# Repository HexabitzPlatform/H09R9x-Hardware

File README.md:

# H09R9x-Hardware
Hexabitz Thermopile Sensor Module Hardware Design

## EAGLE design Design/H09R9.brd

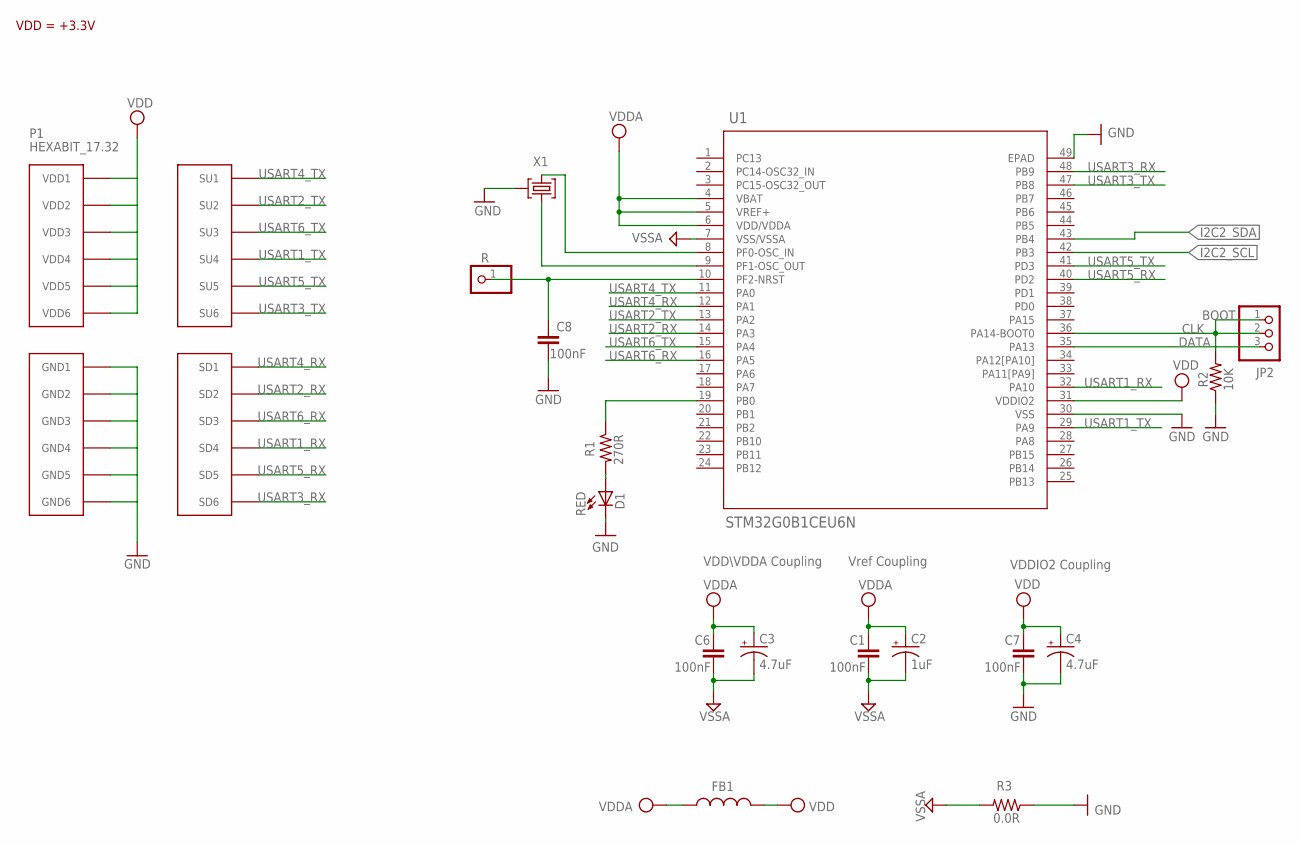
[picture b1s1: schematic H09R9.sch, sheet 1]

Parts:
C1, C6, C7, C8: 100nF; C-0603
C2: 1uF; C-0805-POL
C3, C4: 4.7uF; C-0805-POL
D1: RED; VLMS1300-GS08; MPN VLMS1300-GS08
FB1: FB-TDK_MMZ1608Y300B; MPN MMZ1608Y300B
JP2: PINHD-1X3; 1X03
P1: HEXABIT_17.32
R: R; 1X01
R1: 270R; R-0603
R2: 10K; R-0603
R3: 0.0R; R-0603; MPN RC0603JR-070RL
U1: STM32G0B1CEU6N; HEXABITZ_ICS_QFN_B1CEU6_STM-L
X1: XTALL_CSTCE8M00G52

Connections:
CLK: JP2.1, JP2.2, R2.2, U1.36 (PA14-BOOT0)
DATA: JP2.3, U1.35 (PA13)
GND: C4.2 (-), C7.2, C8.2, D1.C, P1.PAD_PD7 (GND1), P1.PAD_PD8 (GND2), P1.PAD_PD9 (GND3), P1.PAD_PD10 (GND4), P1.PAD_PD11 (GND5), P1.PAD_PD12 (GND6), R2.1, R3.1, U1.30 (VSS), U1.49 (EPAD), X1.P$2 (2); also elsewhere on the board
I2C2_SCL: U1.42 (PB3); also elsewhere on the board
I2C2_SDA: U1.43 (PB4); also elsewhere on the board
unnamed: R1.1, U1.19 (PB0)
unnamed: D1.A, R1.2
unnamed: C8.1, R.1, U1.10 (PF2-NRST)
unnamed: U1.9 (PF1-OSC_OUT), X1.P$1 (1)
unnamed: U1.8 (PF0-OSC_IN), X1.P$3 (3)
USART1_RX: P1.PAD_PD4 (SD4), U1.32 (PA10)
USART1_TX: P1.PAD_PU4 (SU4), U1.29 (PA9)
USART2_RX: P1.PAD_PD2 (SD2), U1.14 (PA3)
USART2_TX: P1.PAD_PU2 (SU2), U1.13 (PA2)
USART3_RX: P1.PAD_PD6 (SD6), U1.48 (PB9)
USART3_TX: P1.PAD_PU6 (SU6), U1.47 (PB8)
USART4_RX: P1.PAD_PD1 (SD1), U1.12 (PA1)
USART4_TX: P1.PAD_PU1 (SU1), U1.11 (PA0)
USART5_RX: P1.PAD_PD5 (SD5), U1.40 (PD2)
USART5_TX: P1.PAD_PU5 (SU5), U1.41 (PD3)
USART6_RX: P1.PAD_PD3 (SD3), U1.16 (PA5)
USART6_TX: P1.PAD_PU3 (SU3), U1.15 (PA4)
VDD: C4.1 (+), C7.1, FB1.2, P1.PAD_PU7 (VDD1), P1.PAD_PU8 (VDD2), P1.PAD_PU9 (VDD3), P1.PAD_PU10 (VDD4), P1.PAD_PU11 (VDD5), P1.PAD_PU12 (VDD6), U1.31 (VDDIO2); also elsewhere on the board
VDDA: C1.1, C2.1 (+), C3.1 (+), C6.1, FB1.1, U1.4 (VBAT), U1.5 (VREF+), U1.6 (VDD/VDDA)
VSSA: C1.2, C2.2 (-), C3.2 (-), C6.2, R3.2, U1.7 (VSS/VSSA)

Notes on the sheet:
VDD = +3.3V
Vref Coupling
VDDIO2 Coupling
VDD\VDDA Coupling
BOOT

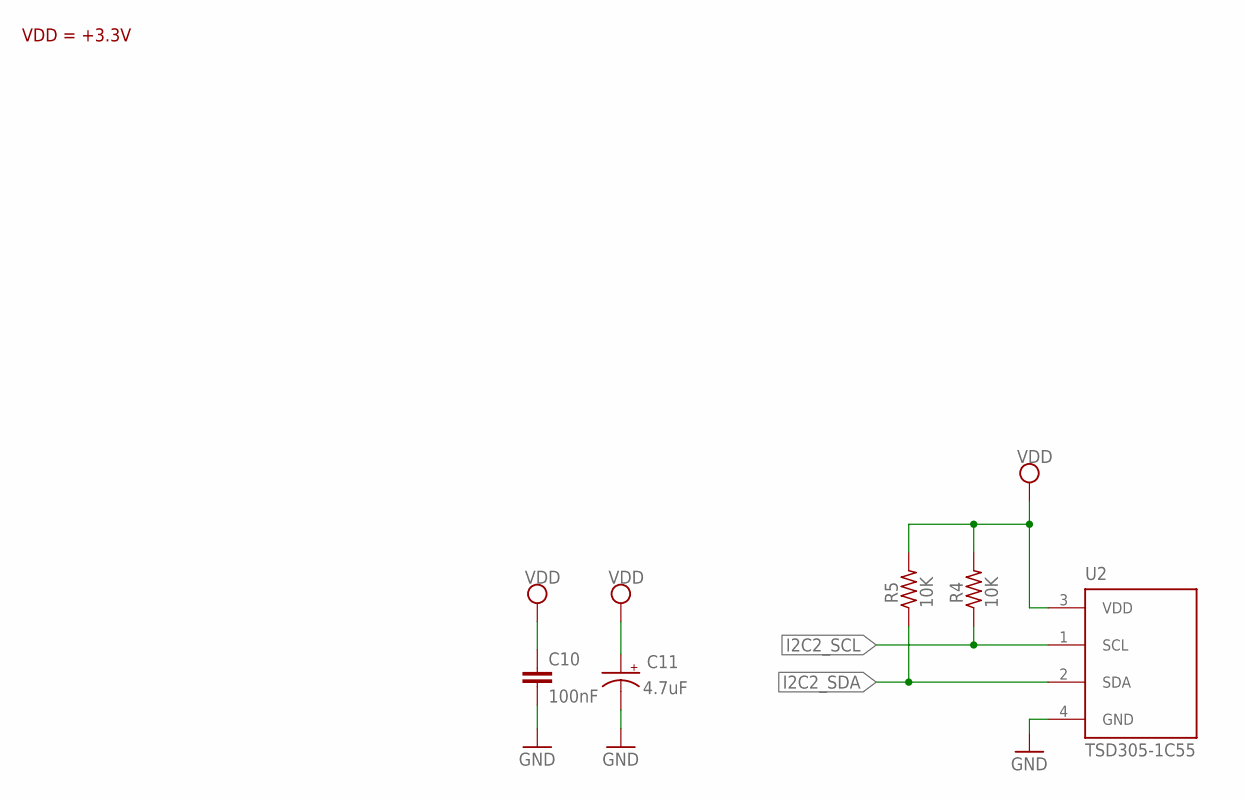
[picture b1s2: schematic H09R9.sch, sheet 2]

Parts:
C10: 100nF; C-0603; TOLERANCE 10%; VOLTAGE_RATING 16.0 V; MPN 0603YC104K4T2A
C11: 4.7uF; C-0805-POL; TOLERANCE 20%; VOLTAGE_RATING 10.0 V; MPN 10TPU4R7MSI
R4, R5: 10K; R-0603
U2: TSD305-1C55; TEMPERATURESENSOR-TO5

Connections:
GND: C10.2, C11.2 (-), U2.4 (GND); also elsewhere on the board
I2C2_SCL: R4.1, U2.1 (SCL); also elsewhere on the board
I2C2_SDA: R5.1, U2.2 (SDA); also elsewhere on the board
VDD: C10.1, C11.1 (+), R4.2, R5.2, U2.3 (VDD); also elsewhere on the board

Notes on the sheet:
VDD = +3.3V

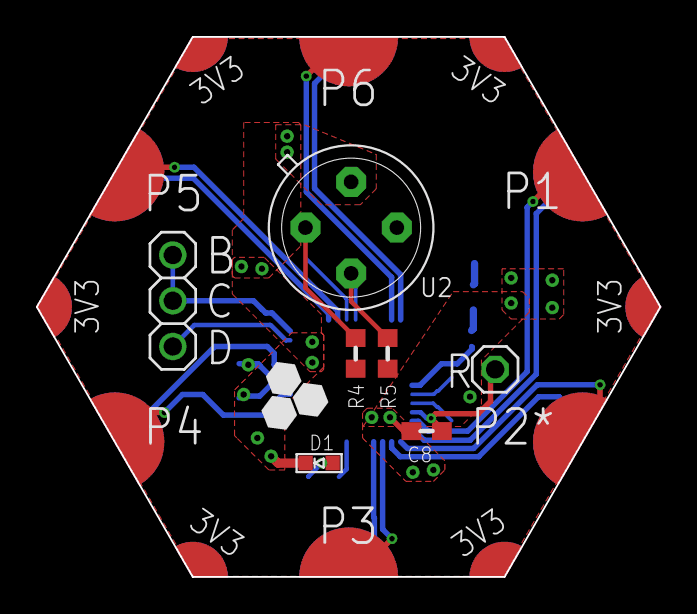
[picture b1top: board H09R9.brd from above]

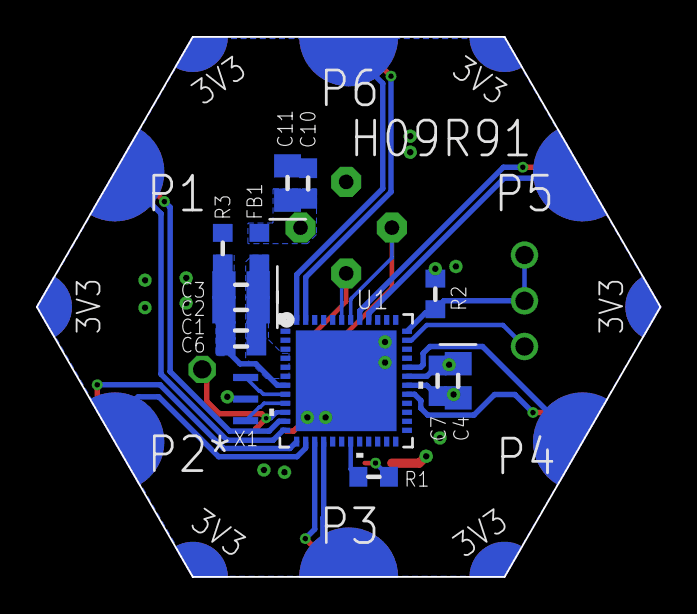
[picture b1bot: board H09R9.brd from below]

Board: 2 copper layers, 34.6 x 30.0 mm, 22 parts (14 on the bottom side), 25 nets.

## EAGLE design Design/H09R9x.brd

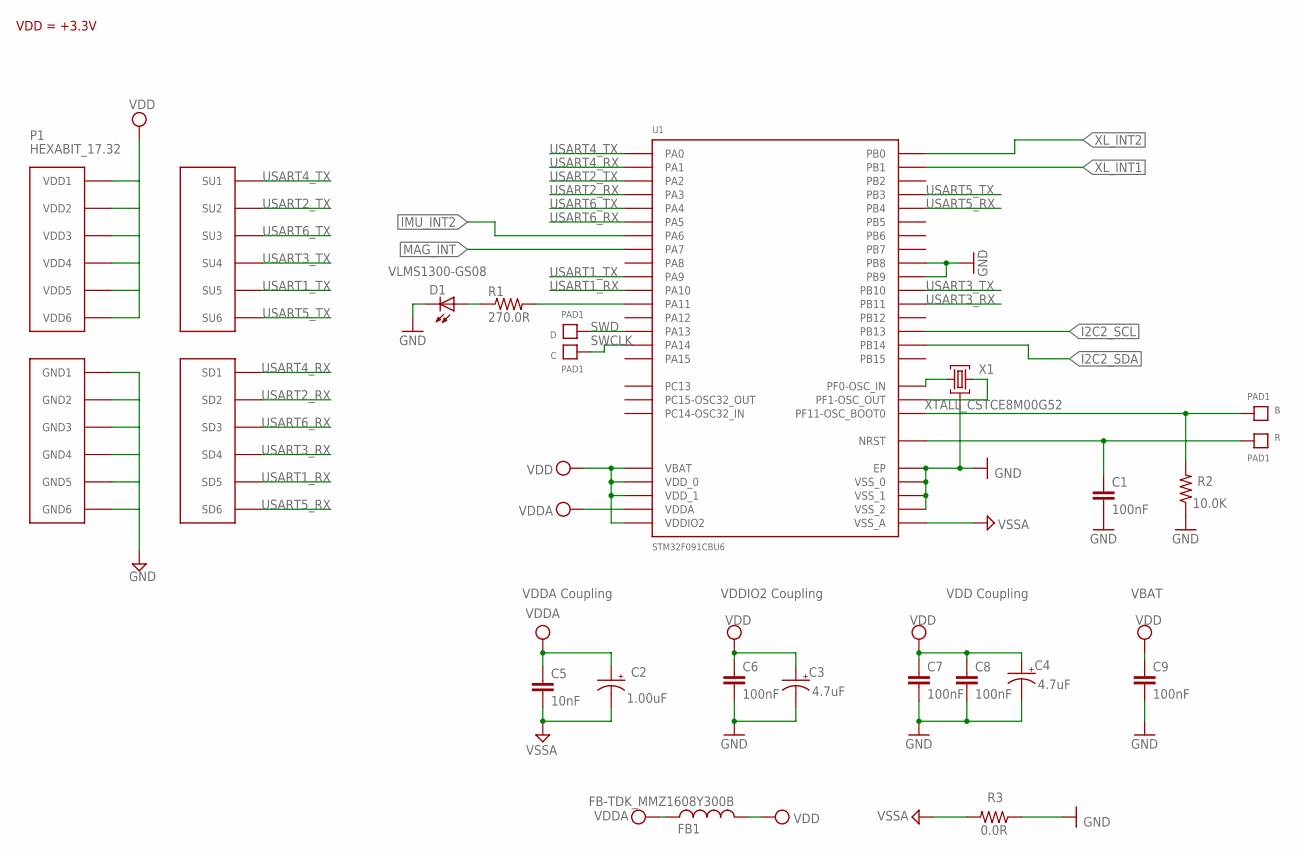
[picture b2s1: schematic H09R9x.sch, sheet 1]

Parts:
B: PAD1
C: PAD1
C1, C6, C7, C8: 100nF; C-0603; TOLERANCE 10%; VOLTAGE_RATING 16.0 V; MPN 0603YC104K4T2A
C2: 1.00uF; C-0805-POL; TOLERANCE 10%; VOLTAGE_RATING 16.0 V; MPN TAJR105M016RNJ
C3: 4.7uF; C-0805-POL; TOLERANCE 20%; VOLTAGE_RATING 10.0 V; MPN 10TPU4R7MSI
C4: 4.7uF; C-0805-POL; TOLERANCE 10%; VOLTAGE_RATING 10 V; MPN 10TPU4R7MSI
C5: 10nF; C-0603; TOLERANCE 10%; VOLTAGE_RATING 16.0 V; MPN 0603YC103KAT4A
C9: 100nF; C-0603; TOLERANCE 16.0 V; VOLTAGE_RATING 10%; MPN 0603YC104K4T2A
D: PAD1
D1: VLMS1300-GS08; MPN VLMS1300-GS08
FB1: FB-TDK_MMZ1608Y300B; MPN MMZ1608Y300B
P1: HEXABIT_17.32
R: PAD1
R1: 270.0R; R-0603; TOLERANCE 5%; MPN ERJ-3GEYJ271V
R2: 10.0K; R-0603; TOLERANCE 5%; MPN CRCW060310K0JNEB
R3: 0.0R; R-0603; MPN CRCW06030000Z0EAHP
U1: STM32F091CBU6
X1: XTALL_CSTCE8M00G52

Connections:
B1: B.P$1, B.P$2, R2.2, U1.P$44 (PF11-OSC_BOOT0)
GND: C1.2, C3.2 (-), C4.2 (-), C6.2, C7.2, C8.2, C9.2, D1.C, P1.PAD_PD7 (GND1), P1.PAD_PD8 (GND2), P1.PAD_PD9 (GND3), P1.PAD_PD10 (GND4), P1.PAD_PD11 (GND5), P1.PAD_PD12 (GND6), R2.1, R3.1, U1.EP, U1.P$23 (VSS_0), U1.P$35 (VSS_1), U1.P$45 (PB8), U1.P$46 (PB9), U1.P$47 (VSS_2), X1.P$2 (2); also elsewhere on the board
I2C2_SCL: U1.P$26 (PB13); also elsewhere on the board
I2C2_SDA: U1.P$27 (PB14); also elsewhere on the board
IMU_INT2: U1.P$16 (PA6)
MAG_INT: U1.P$17 (PA7)
unnamed: R1.2, U1.P$32 (PA11)
unnamed: D1.A, R1.1
unnamed: U1.P$5 (PF0-OSC_IN), X1.P$1 (1)
unnamed: U1.P$6 (PF1-OSC_OUT), X1.P$3 (3)
R1: C1.1, R.P$1, R.P$2, U1.P$7 (NRST)
SWCLK: C.P$1, C.P$2, U1.P$37 (PA14)
SWD: D.P$1, D.P$2, U1.P$34 (PA13)
USART1_RX: P1.PAD_PD5 (SD5), U1.P$31 (PA10)
USART1_TX: P1.PAD_PU5 (SU5), U1.P$30 (PA9)
USART2_RX: P1.PAD_PD2 (SD2), U1.P$13 (PA3)
USART2_TX: P1.PAD_PU2 (SU2), U1.P$12 (PA2)
USART3_RX: P1.PAD_PD4 (SD4), U1.P$22 (PB11)
USART3_TX: P1.PAD_PU4 (SU4), U1.P$21 (PB10)
USART4_RX: P1.PAD_PD1 (SD1), U1.P$11 (PA1)
USART4_TX: P1.PAD_PU1 (SU1), U1.P$10 (PA0)
USART5_RX: P1.PAD_PD6 (SD6), U1.P$40 (PB4)
USART5_TX: P1.PAD_PU6 (SU6), U1.P$39 (PB3)
USART6_RX: P1.PAD_PD3 (SD3), U1.P$15 (PA5)
USART6_TX: P1.PAD_PU3 (SU3), U1.P$14 (PA4)
VDD: C3.1 (+), C4.1 (+), C6.1, C7.1, C8.1, C9.1, FB1.2, P1.PAD_PU7 (VDD1), P1.PAD_PU8 (VDD2), P1.PAD_PU9 (VDD3), P1.PAD_PU10 (VDD4), P1.PAD_PU11 (VDD5), P1.PAD_PU12 (VDD6), U1.P$1 (VBAT), U1.P$24 (VDD_0), U1.P$36 (VDDIO2), U1.P$48 (VDD_1); also elsewhere on the board
VDDA: C2.1 (+), C5.1, FB1.1, U1.P$9 (VDDA)
VSSA: C2.2 (-), C5.2, R3.2, U1.P$8 (VSS_A)
XL_INT1: U1.P$19 (PB1)
XL_INT2: U1.P$18 (PB0)

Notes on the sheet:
VDDA Coupling
VDDIO2 Coupling
VDD Coupling
VBAT
VDD = +3.3V

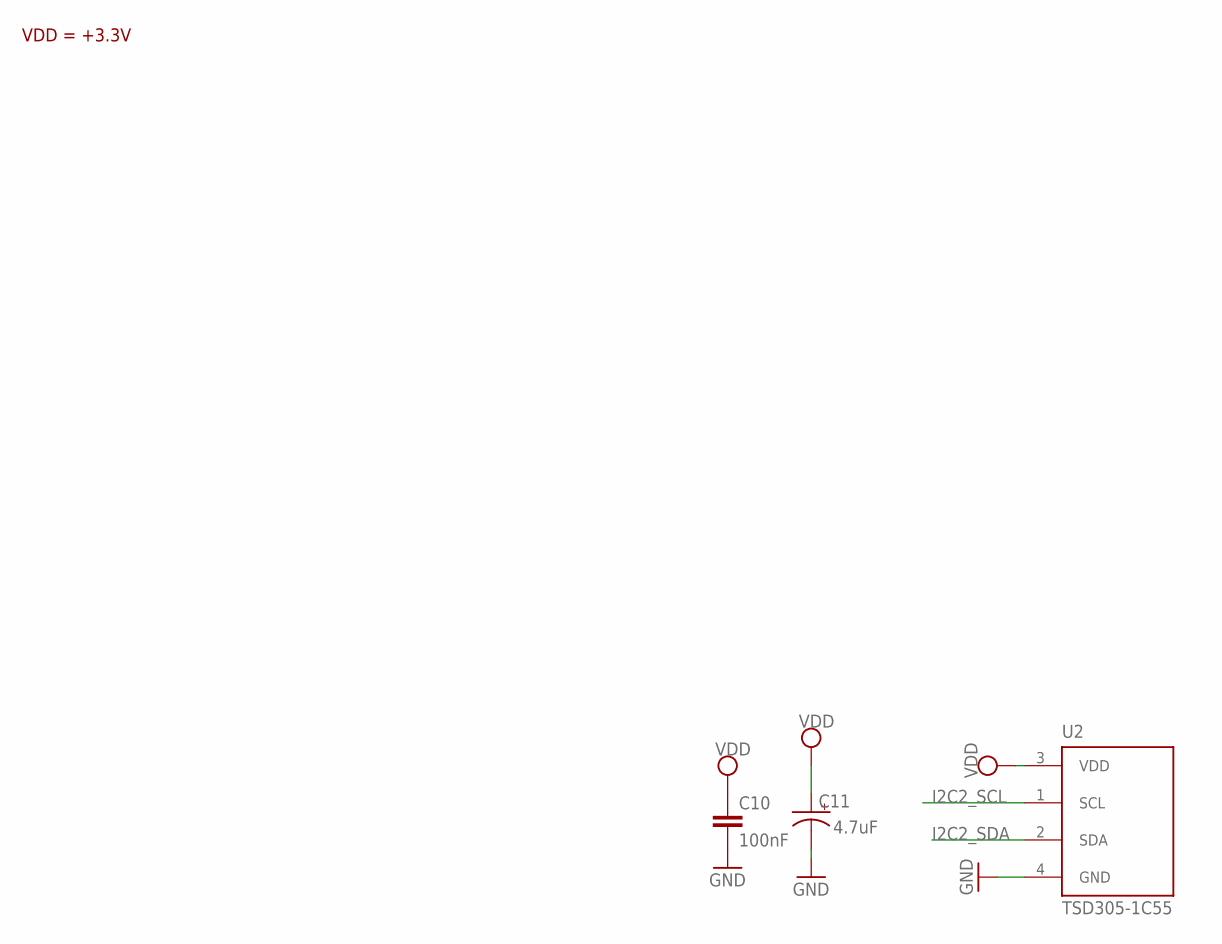
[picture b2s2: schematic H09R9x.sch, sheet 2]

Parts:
C10: 100nF; C-0603; TOLERANCE 10%; VOLTAGE_RATING 16.0 V; MPN 0603YC104K4T2A
C11: 4.7uF; C-0805-POL; TOLERANCE 20%; VOLTAGE_RATING 10.0 V; MPN 10TPU4R7MSI
U2: TSD305-1C55; TEMPERATURESENSOR-TO5

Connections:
GND: C10.2, C11.2 (-), U2.4 (GND); also elsewhere on the board
I2C2_SCL: U2.1 (SCL); also elsewhere on the board
I2C2_SDA: U2.2 (SDA); also elsewhere on the board
VDD: C10.1, C11.1 (+), U2.3 (VDD); also elsewhere on the board

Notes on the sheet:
VDD = +3.3V

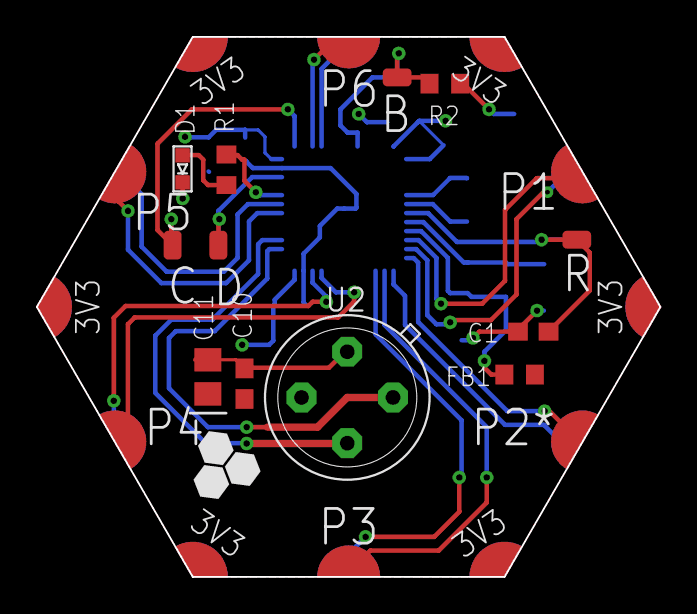
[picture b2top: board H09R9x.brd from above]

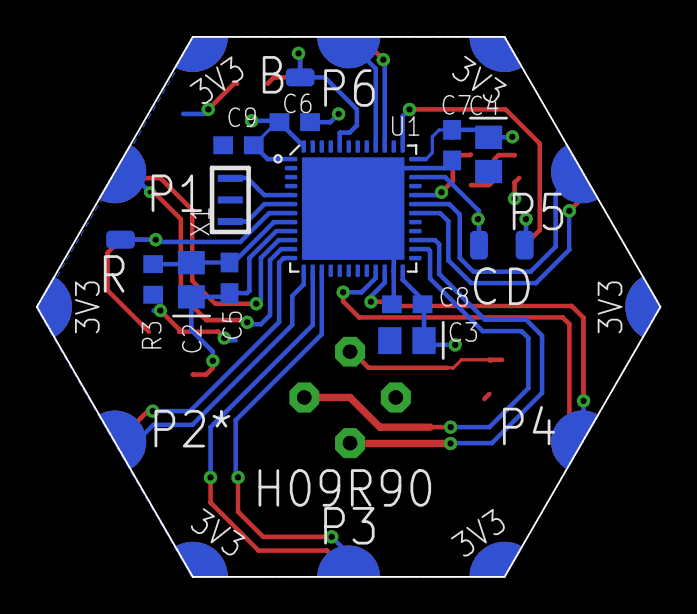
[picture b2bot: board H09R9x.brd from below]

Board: 2 copper layers, 34.6 x 30.0 mm, 24 parts (11 on the bottom side), 26 nets.

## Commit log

2021-03-21 first schematic
2021-03-21 first edit
2021-03-21 not routing yet
2021-03-28 first version sch brd .
2021-03-30 empty
2021-03-31 brd edit
2021-04-16 edit brd
2021-04-20 data upload
2021-04-20 document add
2021-04-20 bom edit
2021-04-20 edit documents
2021-04-20 edit document
2021-04-21 chage thermopile print to last version
2024-01-01 Creat H09R90 folder
2024-01-02 -Standarize the files and folders
2024-02-13 - The reviewed version is complete. - The upgraded version features the STM32G0B1CEU6N MCU. - Pull-up resistors have been added to the I2C Bus.
2024-05-18 Update the BOM

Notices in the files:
parts and their libraries:
HEXABITZ_ICs: COPYRIGHT: Copyright (C) 2022 Ultra Librarian. All rights reserved.
